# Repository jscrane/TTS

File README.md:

View this project on [CADLAB.io](https://cadlab.io/project/1281). 

# TTS

## Text-to-Speech Library for Arduino

- checkout this project into your ``sketchbook/libraries`` folder
- requires an amplifier on the PWM output pin (see below) 
- alternative output via Stream or callback method
- see [blog articles](http://programmablehardware.blogspot.ie/search/label/tts)

## Supported Hardware

- ATmega328-based Arduinos (e.g., Uno, Pro, Pro Mini, etc.): pins 3, 9, 10
- [ArduTouch](https://github.com/maltman23/ArduTouch): pin 9
- ATmega1280-based Arduinos (e.g., Mega): pins 44, 45, 46
- Arduino Leonardo: pin 5
- Arduino Due: pins DAC0 or DAC1
- Teensy 3.2: pin A14
- Teensy 3.5, 3.6: pins A21, A22
- Teensy LC: pin A12
- ESP8266: pins 0 to 16 (with analogWrite())
- ESP32: DAC1 or DAC2 (pins 25 or 26)

## Amplifier

Component choices in this circuit aren't very critical:
- 22k (vs 27k) and 47n (vs 10n) parts in the input low-pass filter 
- 100n (vs 10u) bypass capacitor between pin 7 and gnd
- Used the inverting input instead of the non-inverting one (although in
  this circuit I noticed no difference)
- 47n (vs 100n) output snubber capacitor

## Credits
- original implementation by Clive Webster in [Webbotlib](http://webbot.org.uk/iPoint/30.page)
- ported to Arduino by [Gabriel Petrut](http://www.tehnorama.ro/minieric-modulul-de-control-si-sinteza-vocala/)
- Stephen Crane modified it to use pins other than pin 10 with the help of [this tutorial](https://sites.google.com/site/qeewiki/books/avr-guide/pwm-on-the-atmega328)
- [manitou48](https://github.com/manitou48) added support for Leonardo
and ARM processors with DAC (Teensy, Due)

## See Also
- Teensy [forum](https://forum.pjrc.com/threads/44587-TTS-(Text-to-Speech)-Library-Port)
- separate port/hack for MBED ARM with DAC [repository](https://developer.mbed.org/users/manitou/code/tts/)
- Hackaday article on [LM386 amplifiers](https://hackaday.com/2016/12/07/you-can-have-my-lm386s-when-you-pry-them-from-my-cold-dead-hands/)
- Example on how to use the [Output via Streams](https://www.pschatzmann.ch/home/2021/06/22/text-to-speach-in-arduino-using-tts/)

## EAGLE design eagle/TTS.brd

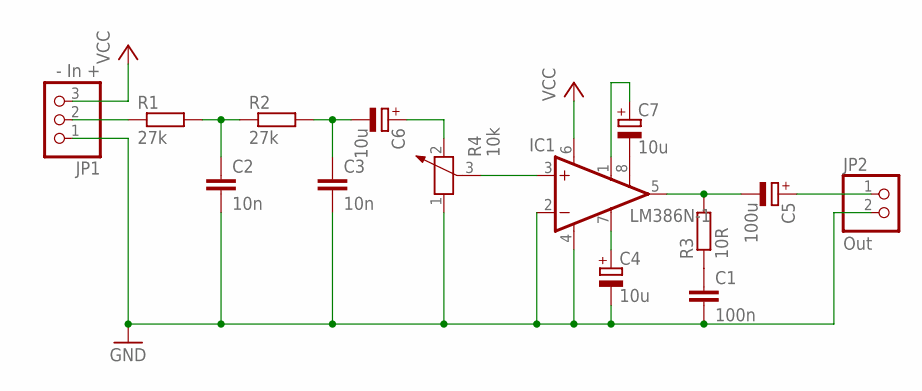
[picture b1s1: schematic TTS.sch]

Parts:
C1: 100n; C050-024X044
C2, C3: 10n; C050-024X044
C4, C6, C7: 10u; E2,5-5
C5: 100u; E2,5-6
IC1: LM386N-1; DIL08
JP1: - In +; 1X03
JP2: Out; 1X02
R1, R2: 27k; 0207/10
R3: 10R; 0207/10
R4: 10k; PT-10S

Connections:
GND: C1.2, C2.2, C3.2, C4.-, IC1.2 (-IN), IC1.4 (GND), JP1.1, JP2.2, R4.1
unnamed: C1.1, R3.1
unnamed: C2.1, R1.2, R2.1
unnamed: C3.1, C6.-, R2.2
unnamed: C4.+, IC1.7 (BYPASS)
unnamed: C5.-, IC1.5 (OUT), R3.2
unnamed: IC1.3 (+IN), R4.3
unnamed: JP1.2, R1.1
unnamed: C5.+, JP2.1
unnamed: C6.+, R4.2
unnamed: C7.-, IC1.8 (GAIN)
unnamed: C7.+, IC1.1 (GAIN)
VCC: IC1.6 (VS), JP1.3

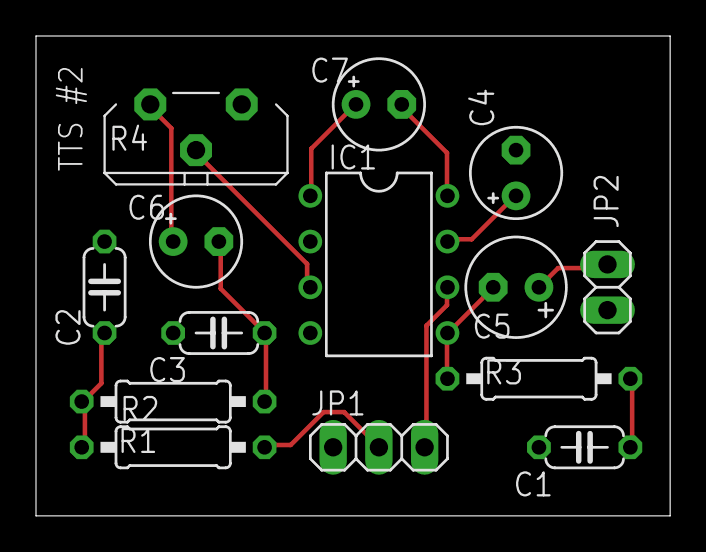
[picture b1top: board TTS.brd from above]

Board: 2 copper layers, 35.2 x 26.7 mm, 14 parts (0 on the bottom side), 13 nets.

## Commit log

2013-02-02 add example
2013-02-02 adding reference to amplifier circuit
2013-02-03 - supporting new port - docs - adding Voice of Tic Bot example
2013-02-04 api change
2013-02-10 adding sound
2014-05-14 fix issue #1
2014-05-14 link to blog
2014-05-30 Added schematic to README.md
2016-08-26 Make TTS.cpp build on Arduino Leonardo
    Any reference to Timer2 registers won't compile on Arduino Leonardo (ATmega32u4). Ifdef out Timer2 references on Leonardo.
2016-09-01 Fix buffer handling issues
    The first bug was that sayText was copying a buffer of up to 112 bytes into a buffer of size 64 (g_text). Fixed it by changing g_text to 128 bytes, plus we don't need to copy the buffer, we can just 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
    The next bug was a line of code was checking to see if we'd written 256-16 bytes to a buffer. All buffers are 128 bytes, so I changed it to 128-16.
    Note that in general this code is likely to produce no output if the input sentence is larger than about 50 to 60 characters (since the final phoneme data will end up being more than 112 characters w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
2017-03-11 mega2560 additions by Peter Dambrowsky
2017-03-14 support pin45 too
2017-06-07 update for Teensy 3 and leonardo pin 5
2017-06-08 conditionalize DACPIN
2017-06-09 for DAC use 4-bit duty
2017-06-10 add DUE DACPIN
2017-11-02 @PlatformIO Library Registry manifest file
2018-01-07 add note about ArduTouch
2018-01-23 remove cruft
2018-01-23 move defaultPitch
2018-01-23 cleanup DACPIN
2018-01-23 more cleanup
2018-01-23 move pin to TTS class; remove annoying line-breaks
2018-01-24 remove defaults
2018-01-25 remove unnecessary analogWrite()
2018-01-25 minor cleanups
2018-01-28 circuit comments
2018-01-31 pgm_read_ptr() != pgm_read_word()
2018-02-01 more cleanups
2018-02-02 fix iso compiler error
2018-04-07 use LED_BUILTIN
2018-05-30 documentation
2018-05-31 cleanups
2018-05-31 break out sound.cpp; add support for esp8266
2018-09-06 support ESP32
2018-09-07 add eagle project
2018-09-07 Backlink to CADLAB.io has been added.
2018-10-20 updates after build #1
2018-10-23 improve board labels
2021-06-16 Support Callback
2021-06-16 Default Pins
2021-06-16 Display default pin
2021-06-16 Spelling
2021-06-16 Remove pin from TTS
2021-06-22 TTS Info
2021-06-23 Readme
2021-10-26 Change Stream to Print
2022-06-09 16bit support
2023-05-07 fix compiler warnings, use LED_BUILTIN and other small changes
